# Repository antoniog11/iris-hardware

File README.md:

# IRIS Ring Hardware
KiCad schematic and PCB design for [IRIS: Wireless ring for vision-based smart home interaction](https://dl.acm.org/doi/10.1145/3654777.3676327).

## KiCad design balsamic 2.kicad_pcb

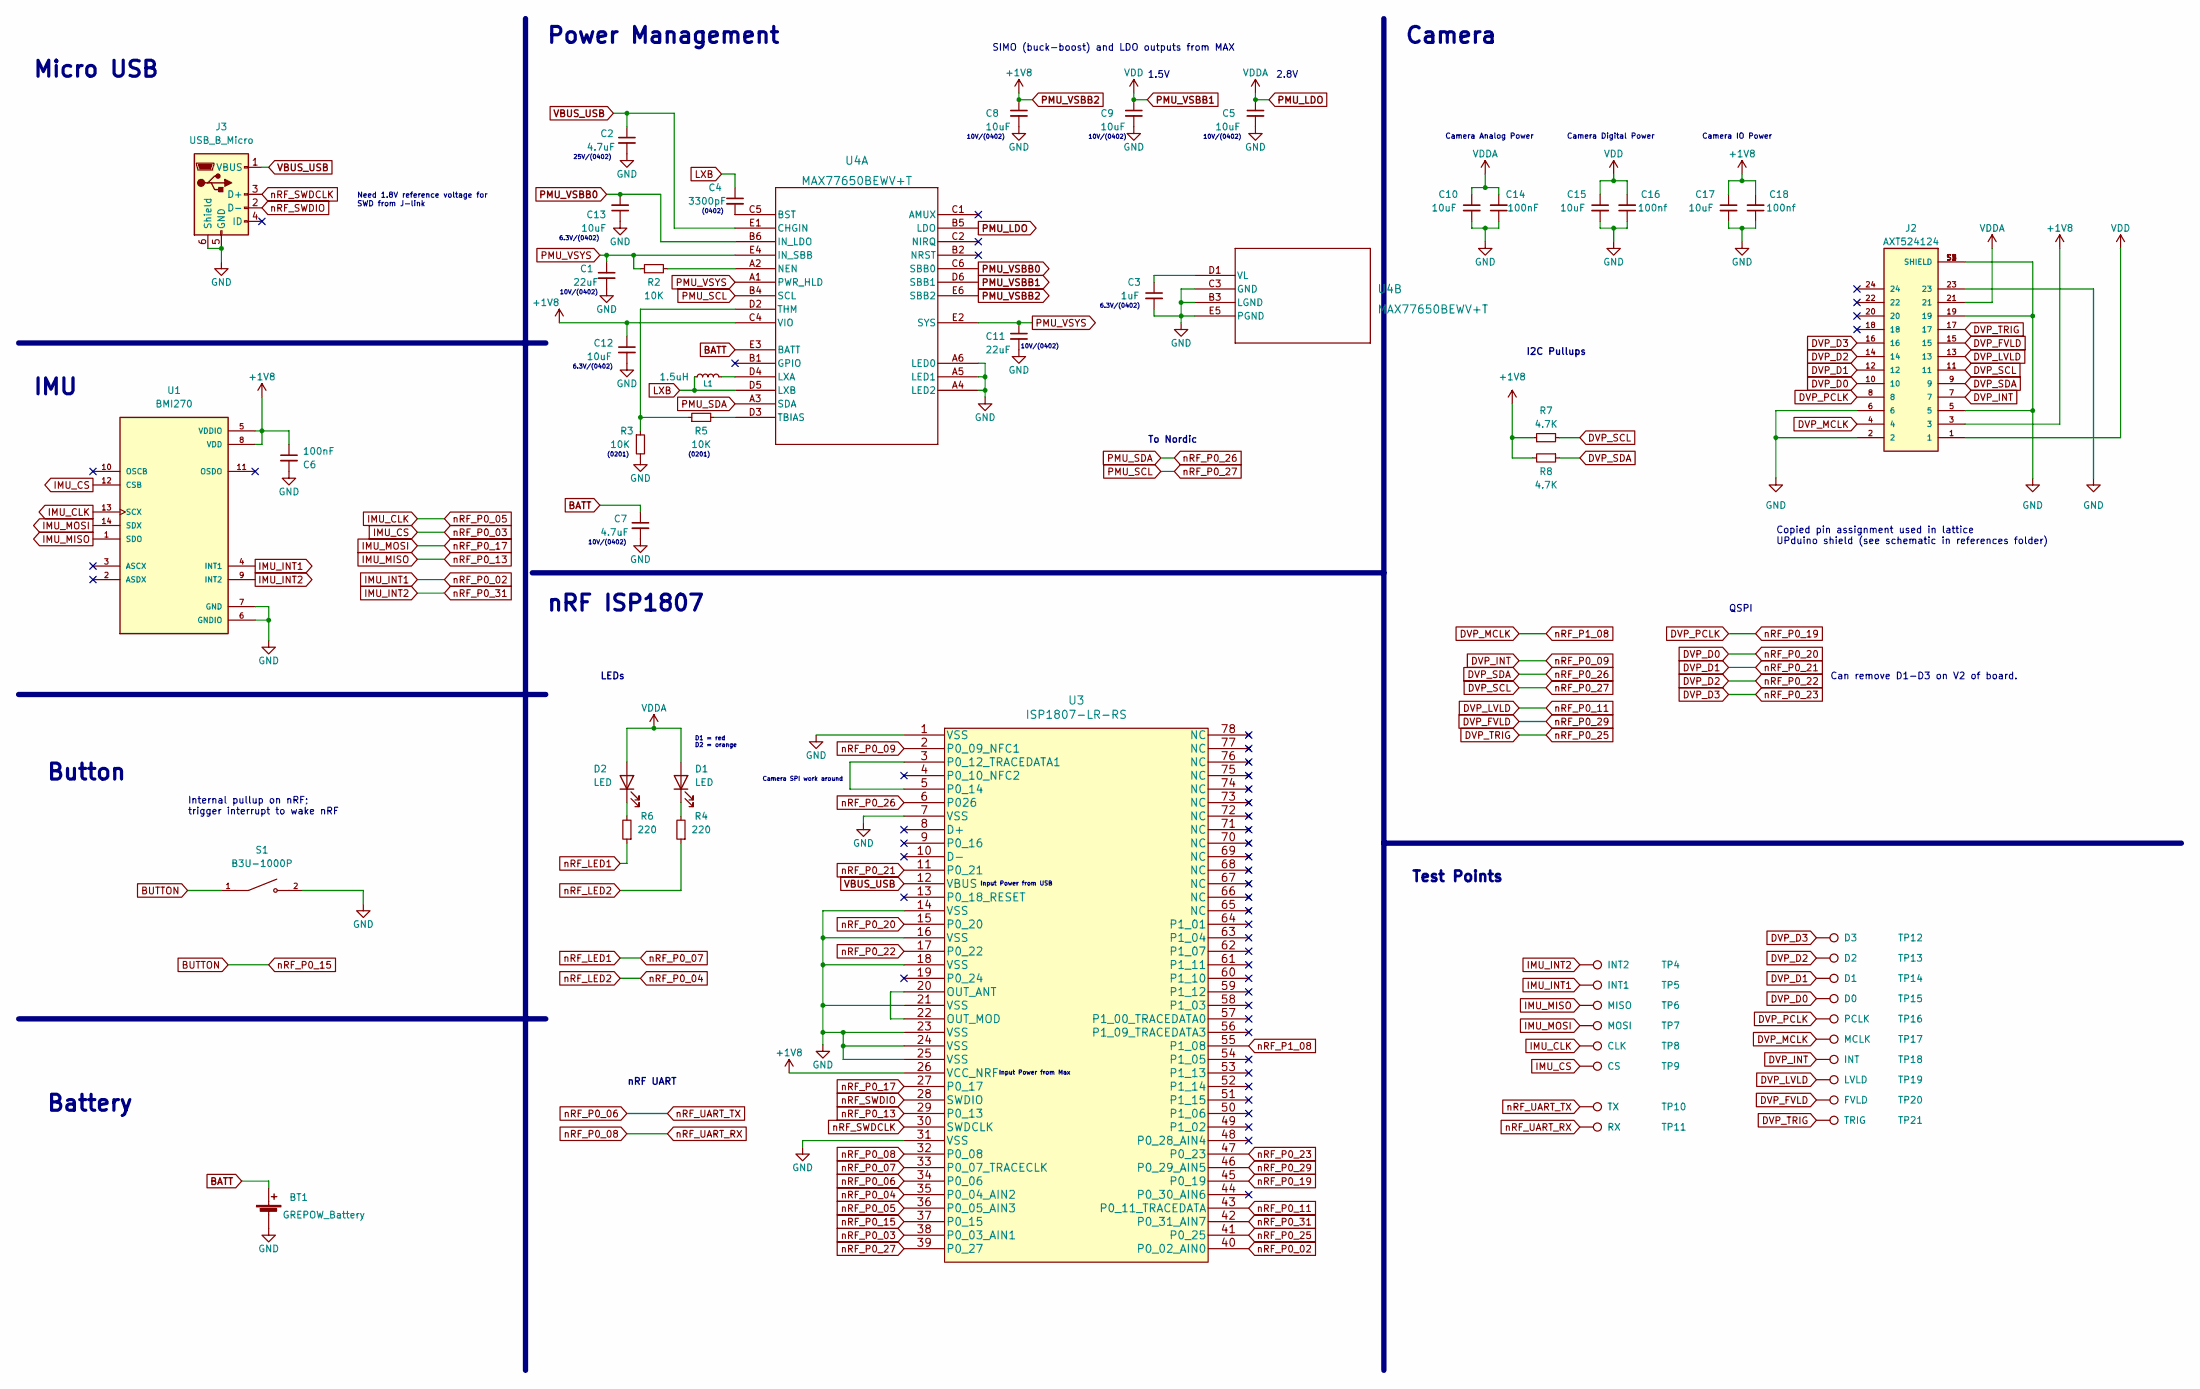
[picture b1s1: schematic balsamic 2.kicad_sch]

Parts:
BT1: GREPOW_Battery; balsamic_grepow_battery
C1, C11: 22uF; C_0402_1005Metric
C2, C7: 4.7uF; C_0402_1005Metric
C3: 1uF; C_0402_1005Metric
C4: 3300pF; C_0402_1005Metric
C5, C8, C9, C12, C13, C15, C17: 10uF; C_0402_1005Metric
C6, C14: 100nF; C_0201_0603Metric
C10: 10uF; C_0402_1005Metric_Pad0.74x0.62mm_HandSolder
C16, C18: 100nf; C_0201_0603Metric
D1, D2: LED; LED_0402_1005Metric
J2: AXT524124; PANASONIC_AXT524124
J3: USB_B_Micro; USB_Micro-B_GCT_USB3076-30-A
L1: 1.5uH; L_0805_2012Metric
R2, R3, R5: 10K; R_0201_0603Metric
R4, R6: 220; R_0201_0603Metric
R7, R8: 4.7K; R_0201_0603Metric
S1: B3U-1000P; SW_B3U-1000P
TP4: INT2; TestPoint_Pad_D0.5mm
TP5: INT1; TestPoint_Pad_D0.5mm
TP6: MISO; TestPoint_Pad_D0.5mm
TP7: MOSI; TestPoint_Pad_D0.5mm
TP8: CLK; TestPoint_Pad_D0.5mm
TP9: CS; TestPoint_Pad_D0.5mm
TP10: TX; TestPoint_Pad_D0.5mm
TP11: RX; TestPoint_Pad_D0.5mm
TP12: D3; TestPoint_Pad_D0.5mm
TP13: D2; TestPoint_Pad_D0.5mm
TP14: D1; TestPoint_Pad_D0.5mm
TP15: D0; TestPoint_Pad_D0.5mm
TP16: PCLK; TestPoint_Pad_D0.5mm
TP17: MCLK; TestPoint_Pad_D0.5mm
TP18: INT; TestPoint_Pad_D0.5mm
TP19: LVLD; TestPoint_Pad_D0.5mm
TP20: FVLD; TestPoint_Pad_D0.5mm
TP21: TRIG; TestPoint_Pad_D0.5mm
U1: BMI270; XDCR_BMI270
U3: ISP1807-LR-RS
U4: MAX77650BEWV+T; 21-100047A_W302H2&plus_1_MXM

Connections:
BATT: BT1.1 (+), C7.1, U4.E3 (BATT); also elsewhere on the board
BUTTON: S1.1, U3.37 (P0_15)
DVP_D0: J2.10, TP15.1, U3.15 (P0_20)
DVP_D1: J2.12, TP14.1, U3.11 (P0_21)
DVP_D2: J2.14, TP13.1, U3.17 (P0_22)
DVP_D3: J2.16, TP12.1, U3.47 (P0_23)
DVP_FVLD: J2.15, TP20.1, U3.46 (P0_29_AIN5)
DVP_INT: J2.7, TP18.1, U3.2 (P0_09_NFC1)
DVP_LVLD: J2.13, TP19.1, U3.43 (P0_11_TRACEDATA)
DVP_MCLK: J2.4, TP17.1, U3.55 (P1_08)
DVP_PCLK: J2.8, TP16.1, U3.45 (P0_19)
DVP_SCL: J2.11, R7.2, U3.39 (P0_27), U4.B4 (SCL)
DVP_SDA: J2.9, R8.1, U3.6 (P026), U4.A3 (SDA)
DVP_TRIG: J2.17, TP21.1, U3.41 (P0_25)
GND: BT1.2 (-), C1.2, C2.2, C3.2, C5.2, C6.2, C7.2, C8.2, C9.2, C10.2, C11.2, C12.2, C13.1, C14.1, C15.2, C16.1, C17.2, C18.1, J2.2, J2.5, J2.6, J2.19, J2.23, J2.S1 (SHIELD), J2.S2 (SHIELD), J2.S3 (SHIELD), J2.S4 (SHIELD), J3.5 (GND), J3.6 (Shield), R3.2, S1.2, U1.6 (GNDIO), U1.7 (GND), U3.1 (VSS), U3.7 (VSS), U3.14 (VSS), U3.16 (VSS), U3.18 (VSS), U3.21 (VSS), U3.23 (VSS), U3.24 (VSS), U3.25 (VSS), U3.31 (VSS), U4.A4 (LED2), U4.A5 (LED1), U4.A6 (LED0), U4.B3 (LGND), U4.C3 (GND), U4.E5 (PGND); also elsewhere on the board
IMU_CLK: TP8.1, U1.13 (SCX), U3.36 (P0_05_AIN3)
IMU_CS: TP9.1, U1.12 (CSB), U3.38 (P0_03_AIN1)
IMU_INT1: TP5.1, U1.4 (INT1), U3.40 (P0_02_AIN0)
IMU_INT2: TP4.1, U1.9 (INT2), U3.42 (P0_31_AIN7)
IMU_MISO: TP6.1, U1.1 (SDO), U3.29 (P0_13)
IMU_MOSI: TP7.1, U1.14 (SDX), U3.27 (P0_17)
LXB: C4.1, L1.1, U4.D5 (LXB)
unnamed: C4.2, U4.C5 (BST)
unnamed: D1.1 (K), R4.2
unnamed: D2.1 (K), R6.2
unnamed: L1.2, U4.D4 (LXA)
unnamed: R2.2, U4.A2 (NEN)
unnamed: R3.1, R5.1, U4.D2 (THM)
unnamed: R5.2, U4.D3 (TBIAS)
unnamed: U3.3 (P0_12_TRACEDATA1), U3.5 (P0_14)
unnamed: U3.20 (OUT_ANT), U3.22 (OUT_MOD)
unnamed: C3.1, U4.D1 (VL)
PMU_LDO: C5.1, C10.1, C14.2, D1.2 (A), D2.2 (A), J2.21, U4.B5 (LDO)
PMU_VSBB0: C13.2, U4.B6 (IN_LDO), U4.C6 (SBB0)
PMU_VSBB1: C9.1, C15.1, C16.2, J2.1, U4.D6 (SBB1)
PMU_VSBB2: C6.1, C8.1, C12.1, C17.1, C18.2, J2.3, R7.1, R8.2, U1.5 (VDDIO), U1.8 (VDD), U3.26 (VCC_NRF), U4.C4 (VIO), U4.E6 (SBB2)
PMU_VSYS: C1.1, C11.1, R2.1, U4.A1 (PWR_HLD), U4.E2 (SYS), U4.E4 (IN_SBB)
VBUS_USB: C2.1, J3.1 (VBUS), U3.12 (VBUS), U4.E1 (CHGIN)
nRF_LED1: R6.1, U3.33 (P0_07_TRACECLK)
nRF_LED2: R4.1, U3.35 (P0_04_AIN2)
nRF_P0_06: TP10.1, U3.34 (P0_06)
nRF_P0_08: TP11.1, U3.32 (P0_08)
nRF_SWDCLK: J3.3 (D+), U3.30 (SWDCLK)
nRF_SWDIO: J3.2 (D-), U3.28 (SWDIO)

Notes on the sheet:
2.8V
Battery
Button
10V/(0402)
D1 = red D2 = orange
1.5V
Camera IO Power
6.3V/(0402)
Input Power from USB
Input Power from Max
Test Points
Camera SPI work around
(0402)
To Nordic
Camera Digital Power
(0201)
nRF ISP1807
Micro USB
Can remove D1-D3 on V2 of board.
Internal pullup on nRF; trigger interrupt to wake nRF
SIMO (buck-boost) and LDO outputs from MAX
Copied pin assignment used in lattice UPduino shield (see schematic in references folder)
Camera Analog Power
LEDs
nRF UART
QSPI
Camera
I2C Pullups
25V/(0402)
Need 1.8V reference voltage for SWD from J-link
IMU
Power Management

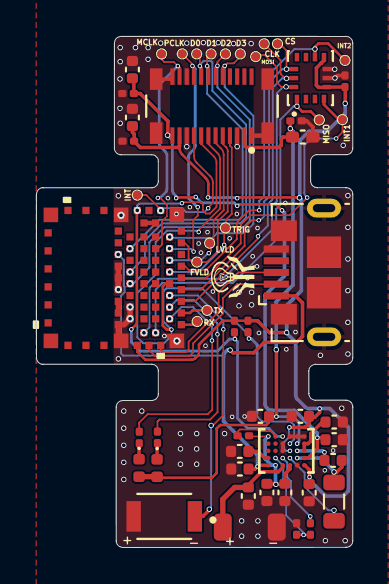
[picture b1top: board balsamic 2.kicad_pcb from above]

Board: 2 copper layers, 17.6 x 28.4 mm, 53 parts (0 on the bottom side), 44 nets.

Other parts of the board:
BT2: GREPOW_Battery; balsamic_grepow_battery

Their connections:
BATT: BT2.1 (+); also elsewhere on the board
GND: BT2.2 (-); also elsewhere on the board

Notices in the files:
parts and their libraries:
Copyright 2021 Accelerated Designs. All rights reserved.
